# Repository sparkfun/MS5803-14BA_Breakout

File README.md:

SparkFun Pressure Sensor Breakout - MS5803-14BA
====================

[*SparkFun Pressure Sensor Breakout - MS5803-14BA (SEN-12909)*](https://www.sparkfun.com/products/12909)

The MS58XX, MS57XX, and MS56XX by Measurement Specialties is a low cost I2C pressure
sensor.  This sensor can be used in weather stations and for altitude
estimations. It can also be used underwater for water depth measurements.

This part was created in Eagle v6.5.0.

Repository Contents
-------------------

* **/Hardware** - All Eagle design files (.brd, .sch)
* **/Libraries** - All Arduino libraries and board examples
* **/Production** - production panel files

Documentation
--------------
* **[Library](https://github.com/sparkfun/SparkFun_MS5803-14BA_Breakout_Arduino_Library)** - Arduino library for the pressure sensor.
* **[Hookup Guide](https://learn.sparkfun.com/tutorials/ms5803-14ba-pressure-sensor-hookup-guide)** - Basic hookup guide for the pressure sensor.
* **[SparkFun Fritzing repo](https://github.com/sparkfun/Fritzing_Parts)** - Fritzing diagrams for SparkFun products.
* **[SparkFun 3D Model repo](https://github.com/sparkfun/3D_Models)** - 3D models of SparkFun products.

Version History
---------------
* [V_H1.0](https://github.com/sparkfun/MS5803-14BA_Breakout/tree/V_H1.0) &mdash; Removing old libraries. Adding links to formal libs in readme.
* [V_H1.0_L1.1.1](https://github.com/sparkfun/MS5803-14BA_Breakout/tree/V_H1.0_L1.1.1) &mdash; Squashed library bugs that truncated data
* [V_H1.0_L1.1.0](https://github.com/sparkfun/MS5803-14BA_Breakout/tree/V_H1.0_L1.1.0) &mdash; Updated library to Arduino 1.6.4
* [v10](https://github.com/sparkfun/MS5803-14BA_Breakout/tree/v1.0) &mdash; Initial Release

License Information
-------------------
This product is _**open source**_!

The **hardware** is released under [Creative Commons ShareAlike 4.0 International](https://creativecommons.org/licenses/by-sa/4.0/).

The **code** is beerware; if you see me (or any other SparkFun employee) at the local, and you've found our code helpful, please buy us a round!

Please use, reuse, and modify these files as you see fit. Please maintain attribution to SparkFun Electronics and release anything derivative under the same license.

Distributed as-is; no warranty is given.

- Your friends at SparkFun.

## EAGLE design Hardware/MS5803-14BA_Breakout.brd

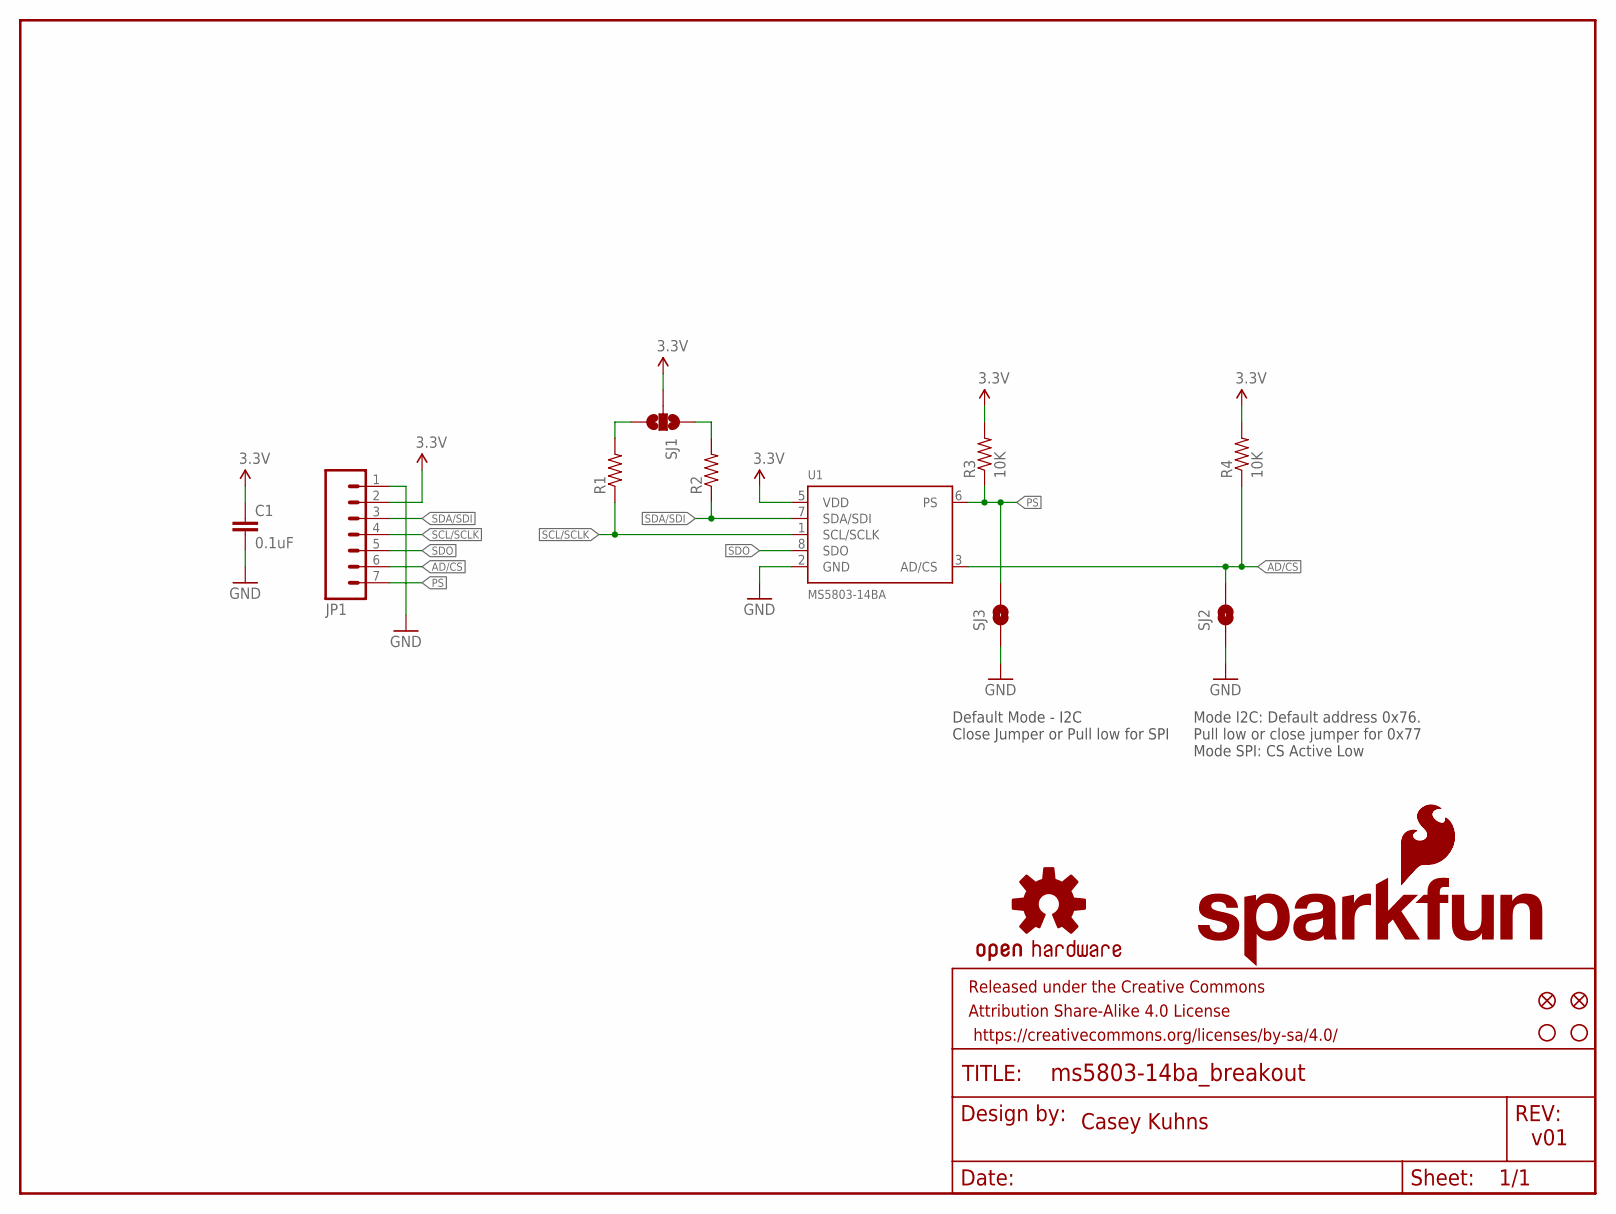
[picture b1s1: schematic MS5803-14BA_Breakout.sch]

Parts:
C1: 0.1uF; 0603-CAP
FID1, FID2: FIDUCIAL1X2; FIDUCIAL-1X2
FRAME1: FRAME-LETTER; CREATIVE_COMMONS
JP1: M07; 1X07
LOGO1: SFE_LOGO_FLAME.1_INCH; SFE_LOGO_FLAME_.1
LOGO2: SFE_LOGO_NAME_FLAME.1_INCH; SFE_LOGO_NAME_FLAME_.1
LOGO3: OSHW-LOGOS; OSHW-LOGO-S
R1, R2: 4.7KOHM1/10W1%(0603); 0603
R3, R4: 10K; 0603-RES
SJ1: SOLDERJUMPER_2WAYPASTE1&2&3; SJ_3_PASTE1&2&3
SJ2, SJ3: SOLDERJUMPERNO; SJ_2S-NO
STANDOFF1, STANDOFF2: STAND-OFFTIGHT; STAND-OFF-TIGHT
U1: MS5803-14BA; MS5803

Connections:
3.3V: C1.1, JP1.2, R3.2, R4.2, SJ1.2, U1.5 (VDD)
AD/CS: JP1.6, R4.1, SJ2.2, U1.3 (AD/CS)
GND: C1.2, JP1.1, SJ2.1, SJ3.1, U1.2 (GND)
unnamed: R1.2, SJ1.3
unnamed: R2.2, SJ1.1
PS: JP1.7, R3.1, SJ3.2, U1.6 (PS)
SCL/SCLK: JP1.4, R1.1, U1.1 (SCL/SCLK)
SDA/SDI: JP1.3, R2.1, U1.7 (SDA/SDI)
SDO: JP1.5, U1.8 (SDO)

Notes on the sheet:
Casey Kuhns
v01
Default Mode - I2C Close Jumper or Pull low for SPI
Mode I2C: Default address 0x76. Pull low or close jumper for 0x77 Mode SPI: CS Active Low

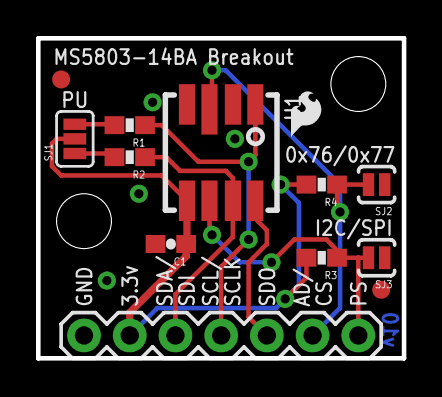
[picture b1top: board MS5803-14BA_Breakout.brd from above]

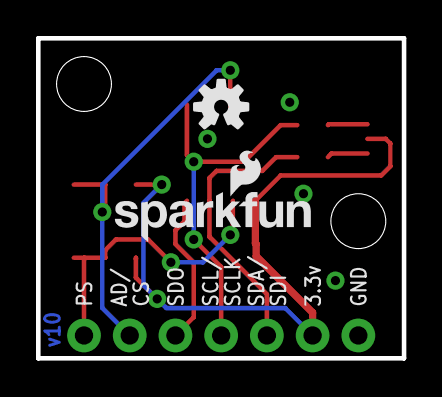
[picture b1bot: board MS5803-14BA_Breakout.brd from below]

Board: 2 copper layers, 20.3 x 17.8 mm, 18 parts (2 on the bottom side), 9 nets.

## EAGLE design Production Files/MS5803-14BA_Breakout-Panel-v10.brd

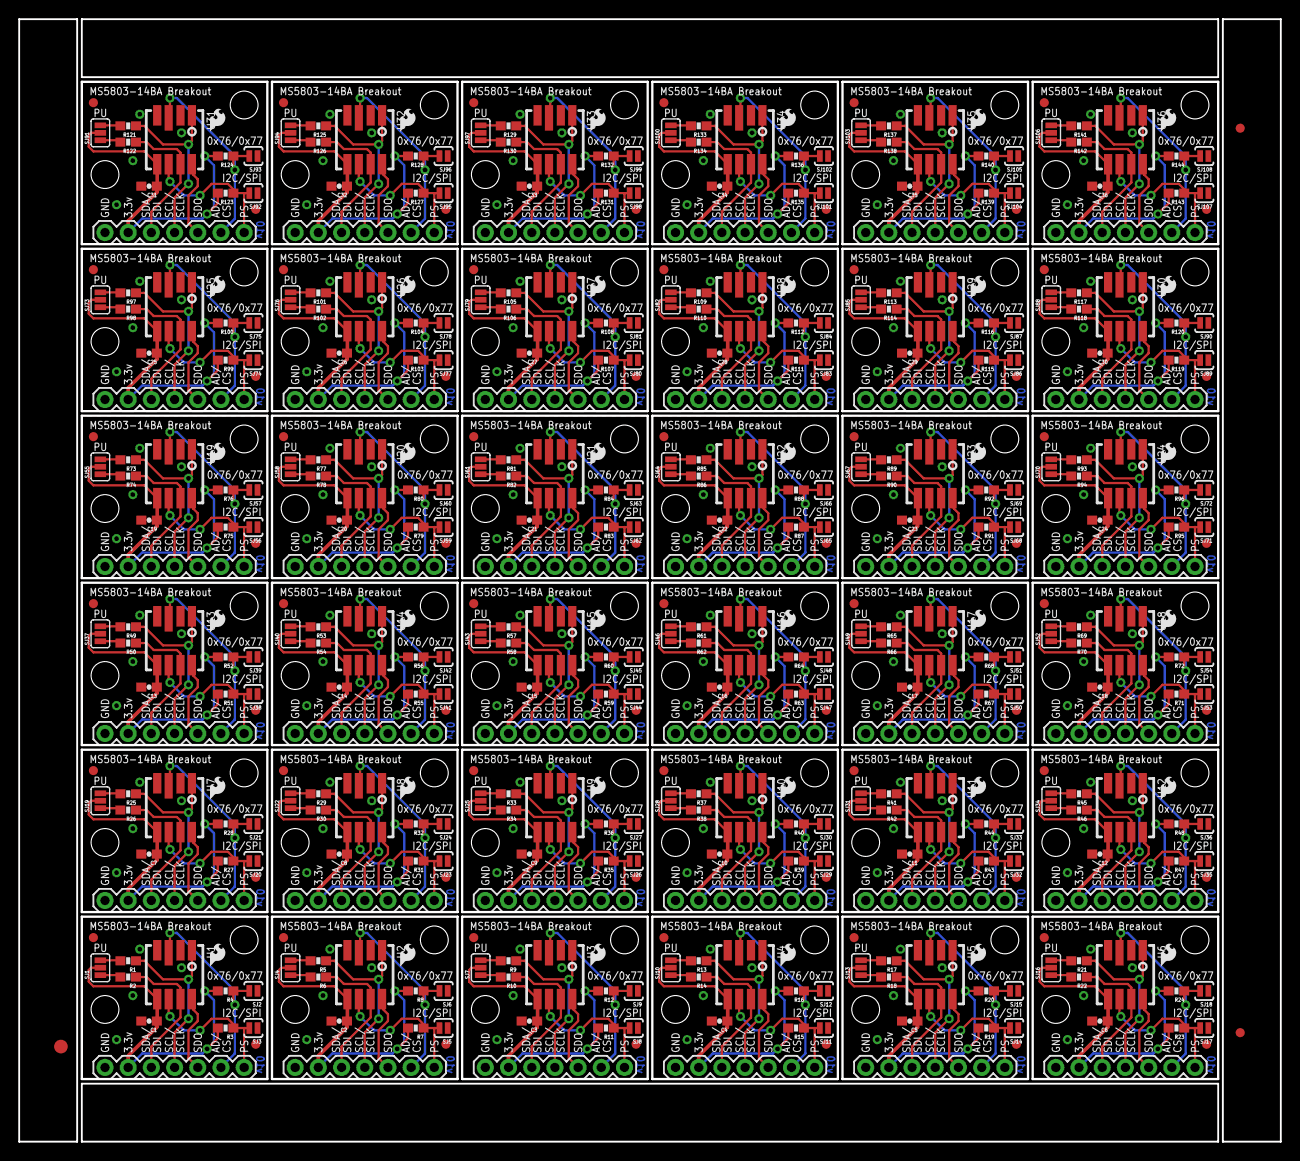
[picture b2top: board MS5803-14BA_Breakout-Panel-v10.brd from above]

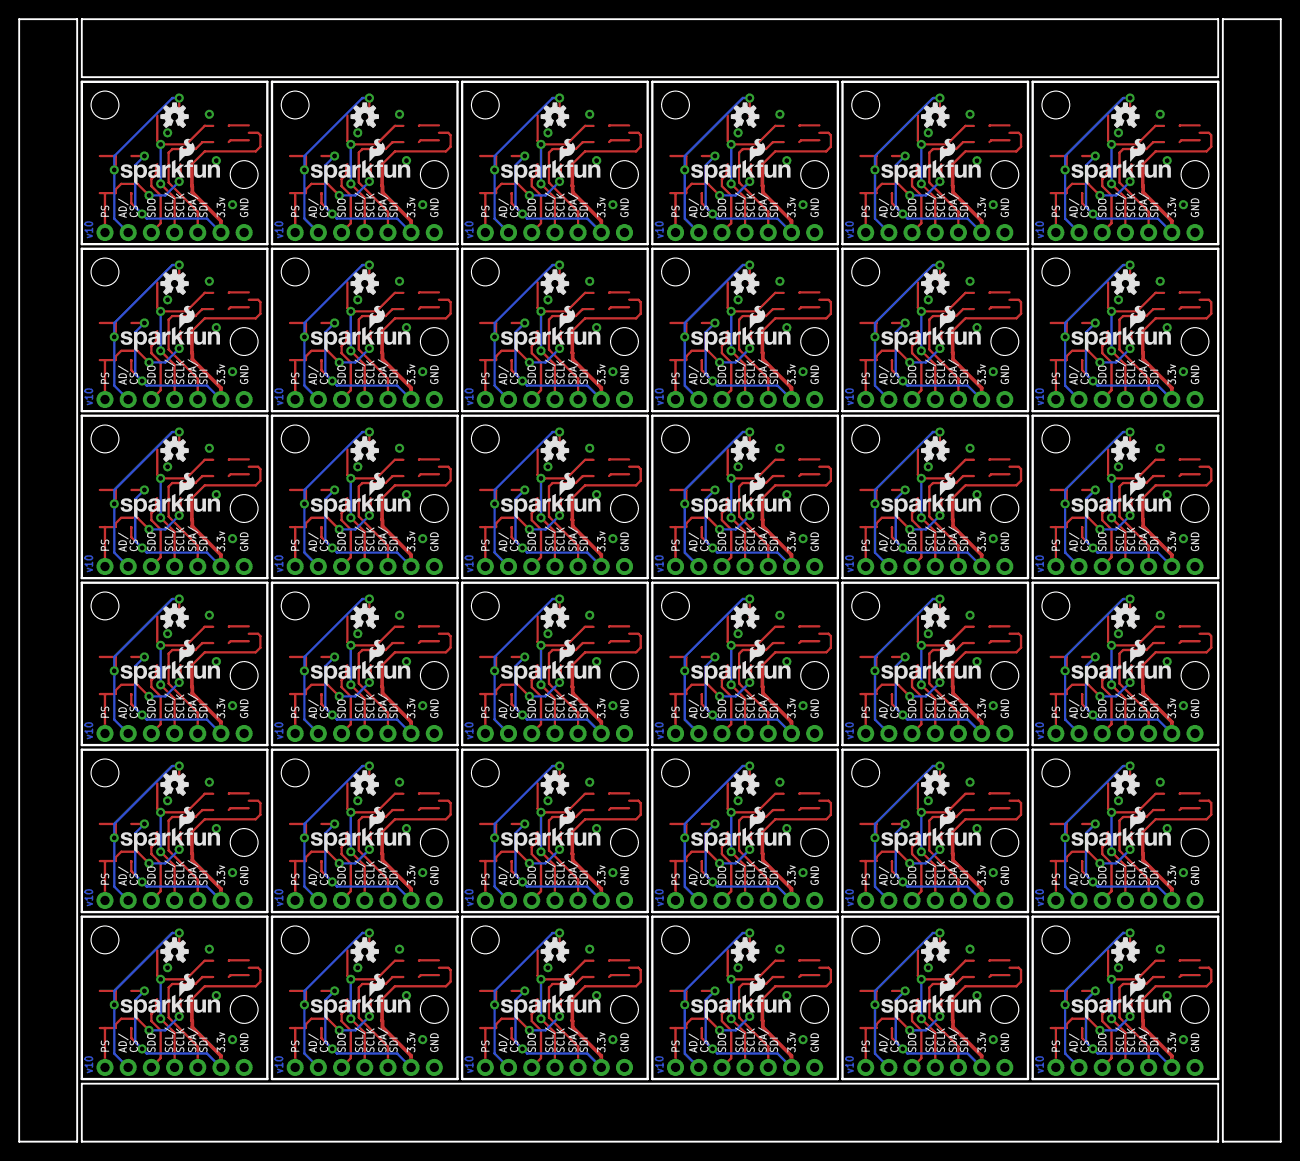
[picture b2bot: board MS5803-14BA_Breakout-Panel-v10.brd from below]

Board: 2 copper layers, 138.2 x 122.9 mm, 615 parts (72 on the bottom side), 324 nets.

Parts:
C1, C2, C3, C4, C5, C6, C7, C8, C9, C10, C11, C12, C13, C14, C15, C16, C17, C18, C19, C20, C21, C22, C23, C24, C25, C26, C27, C28, C29, C30, C31, C32, C33, C34, C35, C36: 0.1uF; 0603-CAP
E$1: FIDUCIAL-1.5X3
E$4, E$6: FIDUCIAL-1X2
FID1, FID2, FID3, FID4, FID5, FID6, FID7, FID8, FID9, FID10, FID11, FID12, FID13, FID14, FID15, FID16, FID17, FID18, FID19, FID20, FID21, FID22, FID23, FID24, FID25, FID26, FID27, FID28, FID29, FID30, FID31, FID32, FID33, FID34, FID35, FID36, FID37, FID38, FID39, FID40, FID41, FID42, FID43, FID44, FID45, FID46, FID47, FID48, FID49, FID50, FID51, FID52, FID53, FID54, FID55, FID56, FID57, FID58, FID59, FID60, FID61, FID62, FID63, FID64, FID65, FID66, FID67, FID68, FID69, FID70, FID71, FID72: FIDUCIAL1X2; FIDUCIAL-1X2
JP1, JP2, JP3, JP4, JP5, JP6, JP7, JP8, JP9, JP10, JP11, JP12, JP13, JP14, JP15, JP16, JP17, JP18, JP19, JP20, JP21, JP22, JP23, JP24, JP25, JP26, JP27, JP28, JP29, JP30, JP31, JP32, JP33, JP34, JP35, JP36: 1X07
LOGO1, LOGO4, LOGO7, LOGO10, LOGO13, LOGO16, LOGO19, LOGO22, LOGO25, LOGO28, LOGO31, LOGO34, LOGO37, LOGO40, LOGO43, LOGO46, LOGO49, LOGO52, LOGO55, LOGO58, LOGO61, LOGO64, LOGO67, LOGO70, LOGO73, LOGO76, LOGO79, LOGO82, LOGO85, LOGO88, LOGO91, LOGO94, LOGO97, LOGO100, LOGO103, LOGO106: SFE_LOGO_FLAME.1_INCH; SFE_LOGO_FLAME_.1
LOGO2, LOGO5, LOGO8, LOGO11, LOGO14, LOGO17, LOGO20, LOGO23, LOGO26, LOGO29, LOGO32, LOGO35, LOGO38, LOGO41, LOGO44, LOGO47, LOGO50, LOGO53, LOGO56, LOGO59, LOGO62, LOGO65, LOGO68, LOGO71, LOGO74, LOGO77, LOGO80, LOGO83, LOGO86, LOGO89, LOGO92, LOGO95, LOGO98, LOGO101, LOGO104, LOGO107: SFE_LOGO_NAME_FLAME.1_INCH; SFE_LOGO_NAME_FLAME_.1
LOGO3, LOGO6, LOGO9, LOGO12, LOGO15, LOGO18, LOGO21, LOGO24, LOGO27, LOGO30, LOGO33, LOGO36, LOGO39, LOGO42, LOGO45, LOGO48, LOGO51, LOGO54, LOGO57, LOGO60, LOGO63, LOGO66, LOGO69, LOGO72, LOGO75, LOGO78, LOGO81, LOGO84, LOGO87, LOGO90, LOGO93, LOGO96, LOGO99, LOGO102, LOGO105, LOGO108: OSHW-LOGOS; OSHW-LOGO-S
R1, R2, R5, R6, R9, R10, R13, R14, R17, R18, R21, R22, R25, R26, R29, R30, R33, R34, R37, R38, R41, R42, R45, R46, R49, R50, R53, R54, R57, R58, R61, R62, R65, R66, R69, R70, R73, R74, R77, R78, R81, R82, R85, R86, R89, R90, R93, R94, R97, R98, R101, R102, R105, R106, R109, R110, R113, R114, R117, R118, R121, R122, R125, R126, R129, R130, R133, R134, R137, R138, R141, R142: 2.2k; 0603-RES
R3, R4, R7, R8, R11, R12, R15, R16, R19, R20, R23, R24, R27, R28, R31, R32, R35, R36, R39, R40, R43, R44, R47, R48, R51, R52, R55, R56, R59, R60, R63, R64, R67, R68, R71, R72, R75, R76, R79, R80, R83, R84, R87, R88, R91, R92, R95, R96, R99, R100, R103, R104, R107, R108, R111, R112, R115, R116, R119, R120, R123, R124, R127, R128, R131, R132, R135, R136, R139, R140, R143, R144: 10K; 0603-RES
SJ1, SJ4, SJ7, SJ10, SJ13, SJ16, SJ19, SJ22, SJ25, SJ28, SJ31, SJ34, SJ37, SJ40, SJ43, SJ46, SJ49, SJ52, SJ55, SJ58, SJ61, SJ64, SJ67, SJ70, SJ73, SJ76, SJ79, SJ82, SJ85, SJ88, SJ91, SJ94, SJ97, SJ100, SJ103, SJ106: PAD-JUMPER-3-NC_BY_PASTE_YES_SILK_FULL_BOX
SJ2, SJ3, SJ5, SJ6, SJ8, SJ9, SJ11, SJ12, SJ14, SJ15, SJ17, SJ18, SJ20, SJ21, SJ23, SJ24, SJ26, SJ27, SJ29, SJ30, SJ32, SJ33, SJ35, SJ36, SJ38, SJ39, SJ41, SJ42, SJ44, SJ45, SJ47, SJ48, SJ50, SJ51, SJ53, SJ54, SJ56, SJ57, SJ59, SJ60, SJ62, SJ63, SJ65, SJ66, SJ68, SJ69, SJ71, SJ72, SJ74, SJ75, SJ77, SJ78, SJ80, SJ81, SJ83, SJ84, SJ86, SJ87, SJ89, SJ90, SJ92, SJ93, SJ95, SJ96, SJ98, SJ99, SJ101, SJ102, SJ104, SJ105, SJ107, SJ108: SOLDERJUMPERNO; SJ_2S-NO
STANDOFF1, STANDOFF2, STANDOFF3, STANDOFF4, STANDOFF5, STANDOFF6, STANDOFF7, STANDOFF8, STANDOFF9, STANDOFF10, STANDOFF11, STANDOFF12, STANDOFF13, STANDOFF14, STANDOFF15, STANDOFF16, STANDOFF17, STANDOFF18, STANDOFF19, STANDOFF20, STANDOFF21, STANDOFF22, STANDOFF23, STANDOFF24, STANDOFF25, STANDOFF26, STANDOFF27, STANDOFF28, STANDOFF29, STANDOFF30, STANDOFF31, STANDOFF32, STANDOFF33, STANDOFF34, STANDOFF35, STANDOFF36, STANDOFF37, STANDOFF38, STANDOFF39, STANDOFF40, STANDOFF41, STANDOFF42, STANDOFF43, STANDOFF44, STANDOFF45, STANDOFF46, STANDOFF47, STANDOFF48, STANDOFF49, STANDOFF50, STANDOFF51, STANDOFF52, STANDOFF53, STANDOFF54, STANDOFF55, STANDOFF56, STANDOFF57, STANDOFF58, STANDOFF59, STANDOFF60, STANDOFF61, STANDOFF62, STANDOFF63, STANDOFF64, STANDOFF65, STANDOFF66, STANDOFF67, STANDOFF68, STANDOFF69, STANDOFF70, STANDOFF71, STANDOFF72: STAND-OFFTIGHT; STAND-OFF-TIGHT
U1, U2, U3, U4, U5, U6, U7, U8, U9, U10, U11, U12, U13, U14, U15, U16, U17, U18, U19, U20, U21, U22, U23, U24, U25, U26, U27, U28, U29, U30, U31, U32, U33, U34, U35, U36: MS5803-14BA; MS5803

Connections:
3.3V: C1.1, JP1.2, R3.2, R4.2, SJ1.2, U1.5
3.3V1: C2.1, JP2.2, R7.2, R8.2, SJ4.2, U2.5
3.3V2: C3.1, JP3.2, R11.2, R12.2, SJ7.2, U3.5
3.3V3: C4.1, JP4.2, R15.2, R16.2, SJ10.2, U4.5
3.3V4: C5.1, JP5.2, R19.2, R20.2, SJ13.2, U5.5
3.3V5: C6.1, JP6.2, R23.2, R24.2, SJ16.2, U6.5
3.3V6: C7.1, JP7.2, R27.2, R28.2, SJ19.2, U7.5
3.3V7: C8.1, JP8.2, R31.2, R32.2, SJ22.2, U8.5
3.3V8: C9.1, JP9.2, R35.2, R36.2, SJ25.2, U9.5
3.3V9: C10.1, JP10.2, R39.2, R40.2, SJ28.2, U10.5
3.3V10: C11.1, JP11.2, R43.2, R44.2, SJ31.2, U11.5
3.3V11: C12.1, JP12.2, R47.2, R48.2, SJ34.2, U12.5
3.3V12: C13.1, JP13.2, R51.2, R52.2, SJ37.2, U13.5
3.3V13: C14.1, JP14.2, R55.2, R56.2, SJ40.2, U14.5
3.3V14: C15.1, JP15.2, R59.2, R60.2, SJ43.2, U15.5
3.3V15: C16.1, JP16.2, R63.2, R64.2, SJ46.2, U16.5
3.3V16: C17.1, JP17.2, R67.2, R68.2, SJ49.2, U17.5
3.3V17: C18.1, JP18.2, R71.2, R72.2, SJ52.2, U18.5
3.3V18: C19.1, JP19.2, R75.2, R76.2, SJ55.2, U19.5
3.3V19: C20.1, JP20.2, R79.2, R80.2, SJ58.2, U20.5
3.3V20: C21.1, JP21.2, R83.2, R84.2, SJ61.2, U21.5
3.3V21: C22.1, JP22.2, R87.2, R88.2, SJ64.2, U22.5
3.3V22: C23.1, JP23.2, R91.2, R92.2, SJ67.2, U23.5
3.3V23: C24.1, JP24.2, R95.2, R96.2, SJ70.2, U24.5
3.3V24: C25.1, JP25.2, R99.2, R100.2, SJ73.2, U25.5
3.3V25: C26.1, JP26.2, R103.2, R104.2, SJ76.2, U26.5
3.3V26: C27.1, JP27.2, R107.2, R108.2, SJ79.2, U27.5
3.3V27: C28.1, JP28.2, R111.2, R112.2, SJ82.2, U28.5
3.3V28: C29.1, JP29.2, R115.2, R116.2, SJ85.2, U29.5
3.3V29: C30.1, JP30.2, R119.2, R120.2, SJ88.2, U30.5
3.3V30: C31.1, JP31.2, R123.2, R124.2, SJ91.2, U31.5
3.3V31: C32.1, JP32.2, R127.2, R128.2, SJ94.2, U32.5
3.3V32: C33.1, JP33.2, R131.2, R132.2, SJ97.2, U33.5
3.3V33: C34.1, JP34.2, R135.2, R136.2, SJ100.2, U34.5
3.3V34: C35.1, JP35.2, R139.2, R140.2, SJ103.2, U35.5
3.3V35: C36.1, JP36.2, R143.2, R144.2, SJ106.2, U36.5
AD/CS: JP1.6, R4.1, SJ2.2, U1.3
AD/CS1: JP2.6, R8.1, SJ6.2, U2.3
AD/CS2: JP3.6, R12.1, SJ9.2, U3.3
AD/CS3: JP4.6, R16.1, SJ12.2, U4.3
AD/CS4: JP5.6, R20.1, SJ15.2, U5.3
AD/CS5: JP6.6, R24.1, SJ18.2, U6.3
AD/CS6: JP7.6, R28.1, SJ21.2, U7.3
AD/CS7: JP8.6, R32.1, SJ24.2, U8.3
AD/CS8: JP9.6, R36.1, SJ27.2, U9.3
AD/CS9: JP10.6, R40.1, SJ30.2, U10.3
AD/CS10: JP11.6, R44.1, SJ33.2, U11.3
AD/CS11: JP12.6, R48.1, SJ36.2, U12.3
AD/CS12: JP13.6, R52.1, SJ39.2, U13.3
AD/CS13: JP14.6, R56.1, SJ42.2, U14.3
AD/CS14: JP15.6, R60.1, SJ45.2, U15.3
AD/CS15: JP16.6, R64.1, SJ48.2, U16.3
AD/CS16: JP17.6, R68.1, SJ51.2, U17.3
AD/CS17: JP18.6, R72.1, SJ54.2, U18.3
AD/CS18: JP19.6, R76.1, SJ57.2, U19.3
AD/CS19: JP20.6, R80.1, SJ60.2, U20.3
AD/CS20: JP21.6, R84.1, SJ63.2, U21.3
AD/CS21: JP22.6, R88.1, SJ66.2, U22.3
AD/CS22: JP23.6, R92.1, SJ69.2, U23.3
AD/CS23: JP24.6, R96.1, SJ72.2, U24.3
AD/CS24: JP25.6, R100.1, SJ75.2, U25.3
AD/CS25: JP26.6, R104.1, SJ78.2, U26.3
AD/CS26: JP27.6, R108.1, SJ81.2, U27.3
AD/CS27: JP28.6, R112.1, SJ84.2, U28.3
AD/CS28: JP29.6, R116.1, SJ87.2, U29.3
AD/CS29: JP30.6, R120.1, SJ90.2, U30.3
AD/CS30: JP31.6, R124.1, SJ93.2, U31.3
AD/CS31: JP32.6, R128.1, SJ96.2, U32.3
AD/CS32: JP33.6, R132.1, SJ99.2, U33.3
AD/CS33: JP34.6, R136.1, SJ102.2, U34.3
AD/CS34: JP35.6, R140.1, SJ105.2, U35.3
AD/CS35: JP36.6, R144.1, SJ108.2, U36.3
GND: C1.2, JP1.1, SJ2.1, SJ3.1, U1.2
GND1: C2.2, JP2.1, SJ5.1, SJ6.1, U2.2
GND2: C3.2, JP3.1, SJ8.1, SJ9.1, U3.2
GND3: C4.2, JP4.1, SJ11.1, SJ12.1, U4.2
GND4: C5.2, JP5.1, SJ14.1, SJ15.1, U5.2
GND5: C6.2, JP6.1, SJ17.1, SJ18.1, U6.2
GND6: C7.2, JP7.1, SJ20.1, SJ21.1, U7.2
GND7: C8.2, JP8.1, SJ23.1, SJ24.1, U8.2
GND8: C9.2, JP9.1, SJ26.1, SJ27.1, U9.2
GND9: C10.2, JP10.1, SJ29.1, SJ30.1, U10.2
GND10: C11.2, JP11.1, SJ32.1, SJ33.1, U11.2
GND11: C12.2, JP12.1, SJ35.1, SJ36.1, U12.2
GND12: C13.2, JP13.1, SJ38.1, SJ39.1, U13.2
GND13: C14.2, JP14.1, SJ41.1, SJ42.1, U14.2
GND14: C15.2, JP15.1, SJ44.1, SJ45.1, U15.2
GND15: C16.2, JP16.1, SJ47.1, SJ48.1, U16.2
GND16: C17.2, JP17.1, SJ50.1, SJ51.1, U17.2
GND17: C18.2, JP18.1, SJ53.1, SJ54.1, U18.2
GND18: C19.2, JP19.1, SJ56.1, SJ57.1, U19.2
GND19: C20.2, JP20.1, SJ59.1, SJ60.1, U20.2
GND20: C21.2, JP21.1, SJ62.1, SJ63.1, U21.2
GND21: C22.2, JP22.1, SJ65.1, SJ66.1, U22.2
GND22: C23.2, JP23.1, SJ68.1, SJ69.1, U23.2
GND23: C24.2, JP24.1, SJ71.1, SJ72.1, U24.2
GND24: C25.2, JP25.1, SJ74.1, SJ75.1, U25.2
GND25: C26.2, JP26.1, SJ77.1, SJ78.1, U26.2
GND26: C27.2, JP27.1, SJ80.1, SJ81.1, U27.2
GND27: C28.2, JP28.1, SJ83.1, SJ84.1, U28.2
GND28: C29.2, JP29.1, SJ86.1, SJ87.1, U29.2
GND29: C30.2, JP30.1, SJ89.1, SJ90.1, U30.2
GND30: C31.2, JP31.1, SJ92.1, SJ93.1, U31.2
GND31: C32.2, JP32.1, SJ95.1, SJ96.1, U32.2
GND32: C33.2, JP33.1, SJ98.1, SJ99.1, U33.2
GND33: C34.2, JP34.1, SJ101.1, SJ102.1, U34.2
GND34: C35.2, JP35.1, SJ104.1, SJ105.1, U35.2
GND35: C36.2, JP36.1, SJ107.1, SJ108.1, U36.2
unnamed: R1.2, SJ1.3
unnamed: R2.2, SJ1.1
unnamed: R5.2, SJ4.3
unnamed: R6.2, SJ4.1
unnamed: R9.2, SJ7.3
unnamed: R10.2, SJ7.1
unnamed: R13.2, SJ10.3
unnamed: R14.2, SJ10.1
unnamed: R17.2, SJ13.3
unnamed: R18.2, SJ13.1
unnamed: R21.2, SJ16.3
unnamed: R22.2, SJ16.1
unnamed: R25.2, SJ19.3
unnamed: R26.2, SJ19.1
unnamed: R29.2, SJ22.3
unnamed: R30.2, SJ22.1
unnamed: R33.2, SJ25.3
unnamed: R34.2, SJ25.1
unnamed: R37.2, SJ28.3
unnamed: R38.2, SJ28.1
unnamed: R41.2, SJ31.3
unnamed: R42.2, SJ31.1
unnamed: R45.2, SJ34.3
unnamed: R46.2, SJ34.1
unnamed: R49.2, SJ37.3
unnamed: R50.2, SJ37.1
unnamed: R53.2, SJ40.3
unnamed: R54.2, SJ40.1
unnamed: R57.2, SJ43.3
unnamed: R58.2, SJ43.1
unnamed: R61.2, SJ46.3
unnamed: R62.2, SJ46.1
unnamed: R65.2, SJ49.3
unnamed: R66.2, SJ49.1
unnamed: R69.2, SJ52.3
unnamed: R70.2, SJ52.1
unnamed: R73.2, SJ55.3
unnamed: R74.2, SJ55.1
unnamed: R77.2, SJ58.3
unnamed: R78.2, SJ58.1
unnamed: R81.2, SJ61.3
unnamed: R82.2, SJ61.1
unnamed: R85.2, SJ64.3
unnamed: R86.2, SJ64.1
unnamed: R89.2, SJ67.3
unnamed: R90.2, SJ67.1
unnamed: R93.2, SJ70.3
unnamed: R94.2, SJ70.1
unnamed: R97.2, SJ73.3
unnamed: R98.2, SJ73.1
unnamed: R101.2, SJ76.3
unnamed: R102.2, SJ76.1
unnamed: R105.2, SJ79.3
unnamed: R106.2, SJ79.1
unnamed: R109.2, SJ82.3
unnamed: R110.2, SJ82.1
unnamed: R113.2, SJ85.3
unnamed: R114.2, SJ85.1
unnamed: R117.2, SJ88.3
unnamed: R118.2, SJ88.1
unnamed: R121.2, SJ91.3
unnamed: R122.2, SJ91.1
unnamed: R125.2, SJ94.3
unnamed: R126.2, SJ94.1
unnamed: R129.2, SJ97.3
unnamed: R130.2, SJ97.1
unnamed: R133.2, SJ100.3
unnamed: R134.2, SJ100.1
unnamed: R137.2, SJ103.3
unnamed: R138.2, SJ103.1
unnamed: R141.2, SJ106.3
unnamed: R142.2, SJ106.1
PS: JP1.7, R3.1, SJ3.2, U1.6
PS1: JP2.7, R7.1, SJ5.2, U2.6
PS2: JP3.7, R11.1, SJ8.2, U3.6
PS3: JP4.7, R15.1, SJ11.2, U4.6
PS4: JP5.7, R19.1, SJ14.2, U5.6
PS5: JP6.7, R23.1, SJ17.2, U6.6
PS6: JP7.7, R27.1, SJ20.2, U7.6
PS7: JP8.7, R31.1, SJ23.2, U8.6
PS8: JP9.7, R35.1, SJ26.2, U9.6
PS9: JP10.7, R39.1, SJ29.2, U10.6
PS10: JP11.7, R43.1, SJ32.2, U11.6
PS11: JP12.7, R47.1, SJ35.2, U12.6
PS12: JP13.7, R51.1, SJ38.2, U13.6
PS13: JP14.7, R55.1, SJ41.2, U14.6
PS14: JP15.7, R59.1, SJ44.2, U15.6
PS15: JP16.7, R63.1, SJ47.2, U16.6
PS16: JP17.7, R67.1, SJ50.2, U17.6
PS17: JP18.7, R71.1, SJ53.2, U18.6
PS18: JP19.7, R75.1, SJ56.2, U19.6
PS19: JP20.7, R79.1, SJ59.2, U20.6
PS20: JP21.7, R83.1, SJ62.2, U21.6
PS21: JP22.7, R87.1, SJ65.2, U22.6
PS22: JP23.7, R91.1, SJ68.2, U23.6
PS23: JP24.7, R95.1, SJ71.2, U24.6
PS24: JP25.7, R99.1, SJ74.2, U25.6
PS25: JP26.7, R103.1, SJ77.2, U26.6
PS26: JP27.7, R107.1, SJ80.2, U27.6
PS27: JP28.7, R111.1, SJ83.2, U28.6
PS28: JP29.7, R115.1, SJ86.2, U29.6
PS29: JP30.7, R119.1, SJ89.2, U30.6
PS30: JP31.7, R123.1, SJ92.2, U31.6
PS31: JP32.7, R127.1, SJ95.2, U32.6
PS32: JP33.7, R131.1, SJ98.2, U33.6
PS33: JP34.7, R135.1, SJ101.2, U34.6
PS34: JP35.7, R139.1, SJ104.2, U35.6
PS35: JP36.7, R143.1, SJ107.2, U36.6
SCL/SCLK: JP1.4, R1.1, U1.1
SCL/SCLK1: JP2.4, R5.1, U2.1
SCL/SCLK2: JP3.4, R9.1, U3.1
SCL/SCLK3: JP4.4, R13.1, U4.1
SCL/SCLK4: JP5.4, R17.1, U5.1
SCL/SCLK5: JP6.4, R21.1, U6.1
SCL/SCLK6: JP7.4, R25.1, U7.1
SCL/SCLK7: JP8.4, R29.1, U8.1
SCL/SCLK8: JP9.4, R33.1, U9.1
SCL/SCLK9: JP10.4, R37.1, U10.1
SCL/SCLK10: JP11.4, R41.1, U11.1
SCL/SCLK11: JP12.4, R45.1, U12.1
SCL/SCLK12: JP13.4, R49.1, U13.1
SCL/SCLK13: JP14.4, R53.1, U14.1
SCL/SCLK14: JP15.4, R57.1, U15.1
SCL/SCLK15: JP16.4, R61.1, U16.1
SCL/SCLK16: JP17.4, R65.1, U17.1
SCL/SCLK17: JP18.4, R69.1, U18.1
SCL/SCLK18: JP19.4, R73.1, U19.1
SCL/SCLK19: JP20.4, R77.1, U20.1
SCL/SCLK20: JP21.4, R81.1, U21.1
SCL/SCLK21: JP22.4, R85.1, U22.1
SCL/SCLK22: JP23.4, R89.1, U23.1
SCL/SCLK23: JP24.4, R93.1, U24.1
SCL/SCLK24: JP25.4, R97.1, U25.1
SCL/SCLK25: JP26.4, R101.1, U26.1
SCL/SCLK26: JP27.4, R105.1, U27.1
SCL/SCLK27: JP28.4, R109.1, U28.1
SCL/SCLK28: JP29.4, R113.1, U29.1
SCL/SCLK29: JP30.4, R117.1, U30.1
SCL/SCLK30: JP31.4, R121.1, U31.1
SCL/SCLK31: JP32.4, R125.1, U32.1
SCL/SCLK32: JP33.4, R129.1, U33.1
SCL/SCLK33: JP34.4, R133.1, U34.1
SCL/SCLK34: JP35.4, R137.1, U35.1
SCL/SCLK35: JP36.4, R141.1, U36.1
SDA/SDI: JP1.3, R2.1, U1.7
SDA/SDI1: JP2.3, R6.1, U2.7
SDA/SDI2: JP3.3, R10.1, U3.7
SDA/SDI3: JP4.3, R14.1, U4.7
SDA/SDI4: JP5.3, R18.1, U5.7
SDA/SDI5: JP6.3, R22.1, U6.7
SDA/SDI6: JP7.3, R26.1, U7.7
SDA/SDI7: JP8.3, R30.1, U8.7
SDA/SDI8: JP9.3, R34.1, U9.7
SDA/SDI9: JP10.3, R38.1, U10.7
SDA/SDI10: JP11.3, R42.1, U11.7
SDA/SDI11: JP12.3, R46.1, U12.7
SDA/SDI12: JP13.3, R50.1, U13.7
SDA/SDI13: JP14.3, R54.1, U14.7
SDA/SDI14: JP15.3, R58.1, U15.7
SDA/SDI15: JP16.3, R62.1, U16.7
SDA/SDI16: JP17.3, R66.1, U17.7
SDA/SDI17: JP18.3, R70.1, U18.7
SDA/SDI18: JP19.3, R74.1, U19.7
SDA/SDI19: JP20.3, R78.1, U20.7
SDA/SDI20: JP21.3, R82.1, U21.7
SDA/SDI21: JP22.3, R86.1, U22.7
SDA/SDI22: JP23.3, R90.1, U23.7
SDA/SDI23: JP24.3, R94.1, U24.7
SDA/SDI24: JP25.3, R98.1, U25.7
SDA/SDI25: JP26.3, R102.1, U26.7
SDA/SDI26: JP27.3, R106.1, U27.7
SDA/SDI27: JP28.3, R110.1, U28.7
SDA/SDI28: JP29.3, R114.1, U29.7
SDA/SDI29: JP30.3, R118.1, U30.7
SDA/SDI30: JP31.3, R122.1, U31.7
SDA/SDI31: JP32.3, R126.1, U32.7
SDA/SDI32: JP33.3, R130.1, U33.7
SDA/SDI33: JP34.3, R134.1, U34.7
SDA/SDI34: JP35.3, R138.1, U35.7
SDA/SDI35: JP36.3, R142.1, U36.7
SDO: JP1.5, U1.8
SDO1: JP2.5, U2.8
SDO2: JP3.5, U3.8
SDO3: JP4.5, U4.8
SDO4: JP5.5, U5.8
SDO5: JP6.5, U6.8
SDO6: JP7.5, U7.8
SDO7: JP8.5, U8.8
SDO8: JP9.5, U9.8
SDO9: JP10.5, U10.8
SDO10: JP11.5, U11.8
SDO11: JP12.5, U12.8
SDO12: JP13.5, U13.8
SDO13: JP14.5, U14.8
SDO14: JP15.5, U15.8
SDO15: JP16.5, U16.8
SDO16: JP17.5, U17.8
SDO17: JP18.5, U18.8
SDO18: JP19.5, U19.8
SDO19: JP20.5, U20.8
SDO20: JP21.5, U21.8
SDO21: JP22.5, U22.8
SDO22: JP23.5, U23.8
SDO23: JP24.5, U24.8
SDO24: JP25.5, U25.8
SDO25: JP26.5, U26.8
SDO26: JP27.5, U27.8
SDO27: JP28.5, U28.8
SDO28: JP29.5, U29.8
SDO29: JP30.5, U30.8
SDO30: JP31.5, U31.8
SDO31: JP32.5, U32.8
SDO32: JP33.5, U33.8
SDO33: JP34.5, U34.8
SDO34: JP35.5, U35.8
SDO35: JP36.5, U36.8

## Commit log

2014-04-29 Inital Board Commit
2014-05-28 changed I2C resistors to 2.2k, updated rev numbers, Moved to new jumper package
2014-05-29 created panel v10
2014-06-27 added Libraries
2014-07-09 worked on libs
2014-07-22 worked on Library heavily
2014-07-24 i2c lib mostly working still fighting a compiler error on pressure measurement
2014-07-24 cleaned up arduino library and got functionality working again.
2014-07-24 removed debug statements
2014-08-06 Fixed Silk
2014-08-08 re-created panel v10
2015-05-14 Updating product repo with proper directory names, adding READMEs
2015-05-14 Removing duplicate license file
2015-05-14 Squashed 'Libraries/Arduino/' content from commit 7959416
    git-subtree-dir: Libraries/Arduino
    git-subtree-split: 7959416012d0d9cc785366e49c315997233704ae
2015-05-14 Adding subtree directions to library readme
2015-05-14 Update README.md
    Fixing readme typo.
2016-01-20 Updated README to account for library update
2016-01-20 Squashed 'Libraries/Arduino/' changes from 7959416..d5c5c9f
    d5c5c9f Added version notes
    c0eb746 Fixed product image URL
    b500377 Fixed floating point math, initialized variables, and cleaned up style
    git-subtree-dir: Libraries/Arduino
    git-subtree-split: d5c5c9f44fd23db86df1f56954f548324cc2ff2a
2019-05-07 Removing old libraries. Adding links to formal libs in readme.
    - Removing subtree and linking to Arduino library repo to keep up with the latest changes in code.

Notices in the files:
parts and their libraries:
SparkFun-Aesthetics: Licensing: Creative Commons ShareAlike 4.0 International - https://creativecommons.org/licenses/by-sa/4.0
SparkFun-Aesthetics: Released under the Creative Commons Attribution Share-Alike 4.0 License
SparkFun-Aesthetics: Released under the Creative Commons
